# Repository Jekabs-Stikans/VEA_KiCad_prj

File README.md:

# VEA_KiCad_prj
This directory will be utilised for projects in the "Datorizētā iespiedplašu projektēšana" course

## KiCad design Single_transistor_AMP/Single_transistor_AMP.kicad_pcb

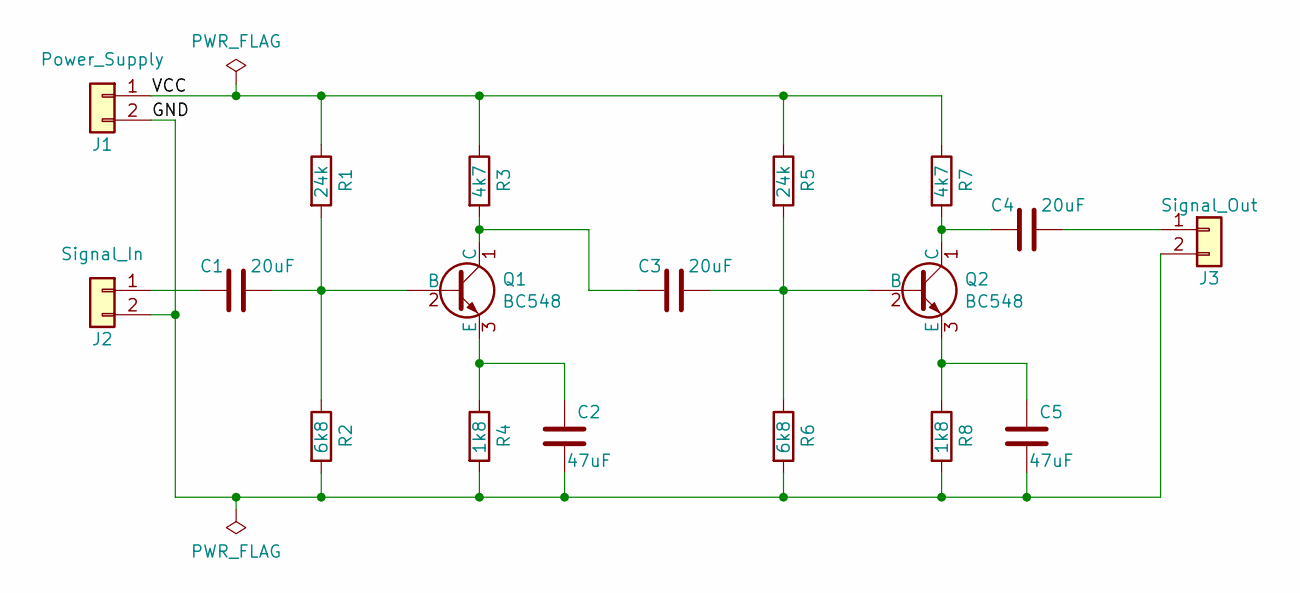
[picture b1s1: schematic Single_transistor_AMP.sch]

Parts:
C1, C3, C4: 20uF; C_1206_HandSoldering
C2, C5: 47uF; C_1206_HandSoldering
J1: Power_Supply; TerminalBlock_bornier-2_P5.08mm
J2: Signal_In; TerminalBlock_bornier-2_P5.08mm
J3: Signal_Out; TerminalBlock_bornier-2_P5.08mm
Q1, Q2: BC548; TO-92_Inline_Narrow_Oval
R1, R5: 24k; R_1206_HandSoldering
R2, R6: 6k8; R_1206_HandSoldering
R3, R7: 4k7; R_1206_HandSoldering
R4, R8: 1k8; R_1206_HandSoldering

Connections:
/GND: C2.1, C5.1, J1.2, J2.2, J3.2, R2.2, R4.2, R6.2, R8.2
/VCC: J1.1, R1.1, R3.1, R5.1, R7.1
unnamed: C1.1, Q1.2 (B), R1.2, R2.1
unnamed: C1.2, J2.1
unnamed: C2.2, Q1.3 (E), R4.1
unnamed: C3.1, Q2.2 (B), R5.2, R6.1
unnamed: C3.2, Q1.1 (C), R3.2
unnamed: C4.1, J3.1
unnamed: C4.2, Q2.1 (C), R7.2
unnamed: C5.2, Q2.3 (E), R8.1

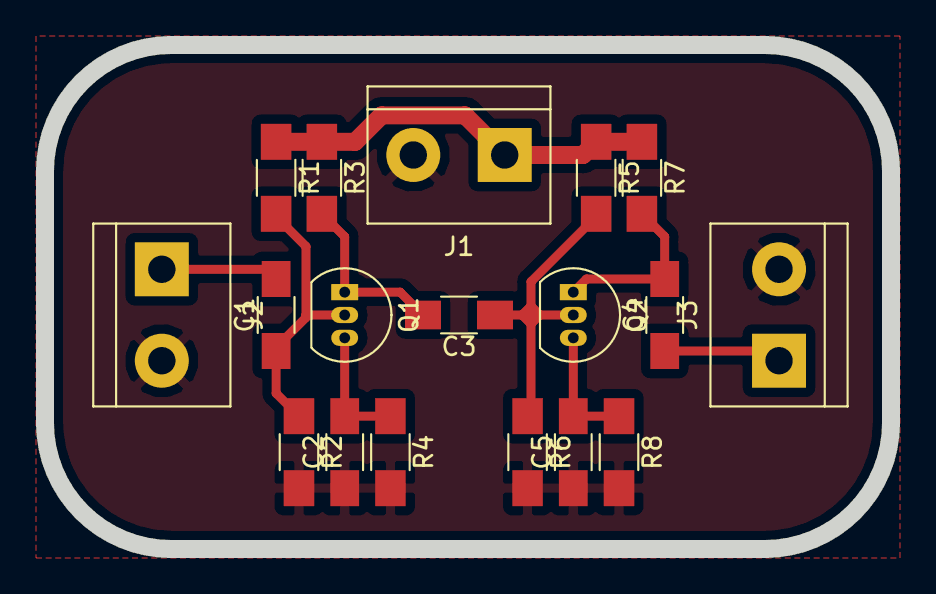
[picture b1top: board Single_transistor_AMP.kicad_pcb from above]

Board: 2 copper layers, 47.0 x 28.0 mm, 18 parts (0 on the bottom side), 10 nets.

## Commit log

2020-10-01 The first README edit
2020-10-01 README text correction
2020-10-01 -l1 file deletion
2020-10-07 KiCad Multivib project created
2020-10-07 Recreated example multivibrator schematic
2020-10-07 Created dual NPN transistor IC symbol
2020-10-07 Multivibrator schematic modification with the new symbol + some corrections
2020-10-10 PWR_Supply v1.0
2020-10-19 Single_transistor_AMP v1.0
2020-11-20 Battery Footprints 1.0
2020-11-20 Battery project netlist
2020-11-20 Battery Footprints 1.1
2020-11-26 Single_transistor_AMP PCB parameter setup
2020-11-26 Single_Transistor_AMP PCB Layout created
2020-12-08 Single_Transistor_AMP PCB routing
2020-12-08 Single_Transistor_AMP gerber file creation
2021-03-26 Post production faili
